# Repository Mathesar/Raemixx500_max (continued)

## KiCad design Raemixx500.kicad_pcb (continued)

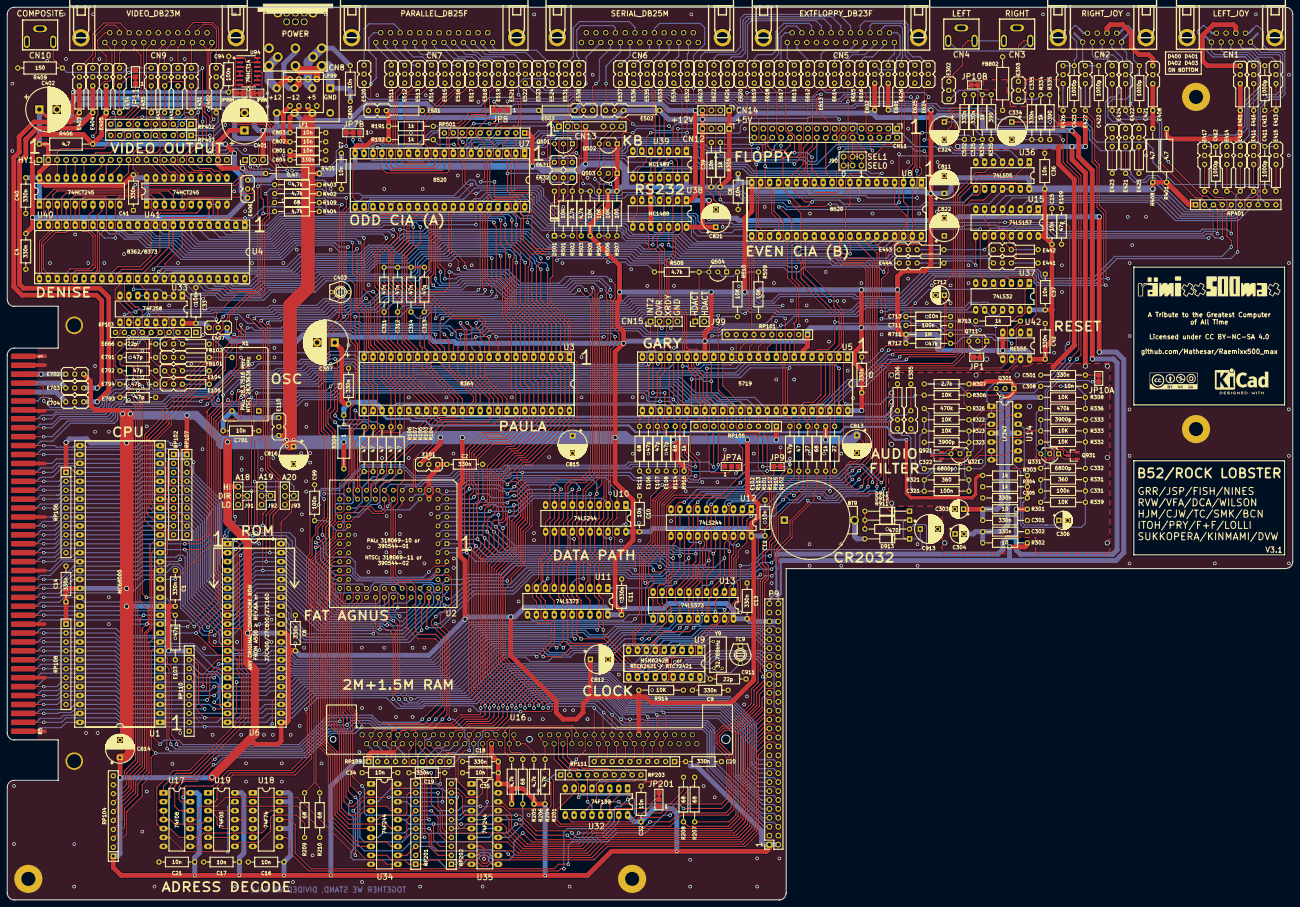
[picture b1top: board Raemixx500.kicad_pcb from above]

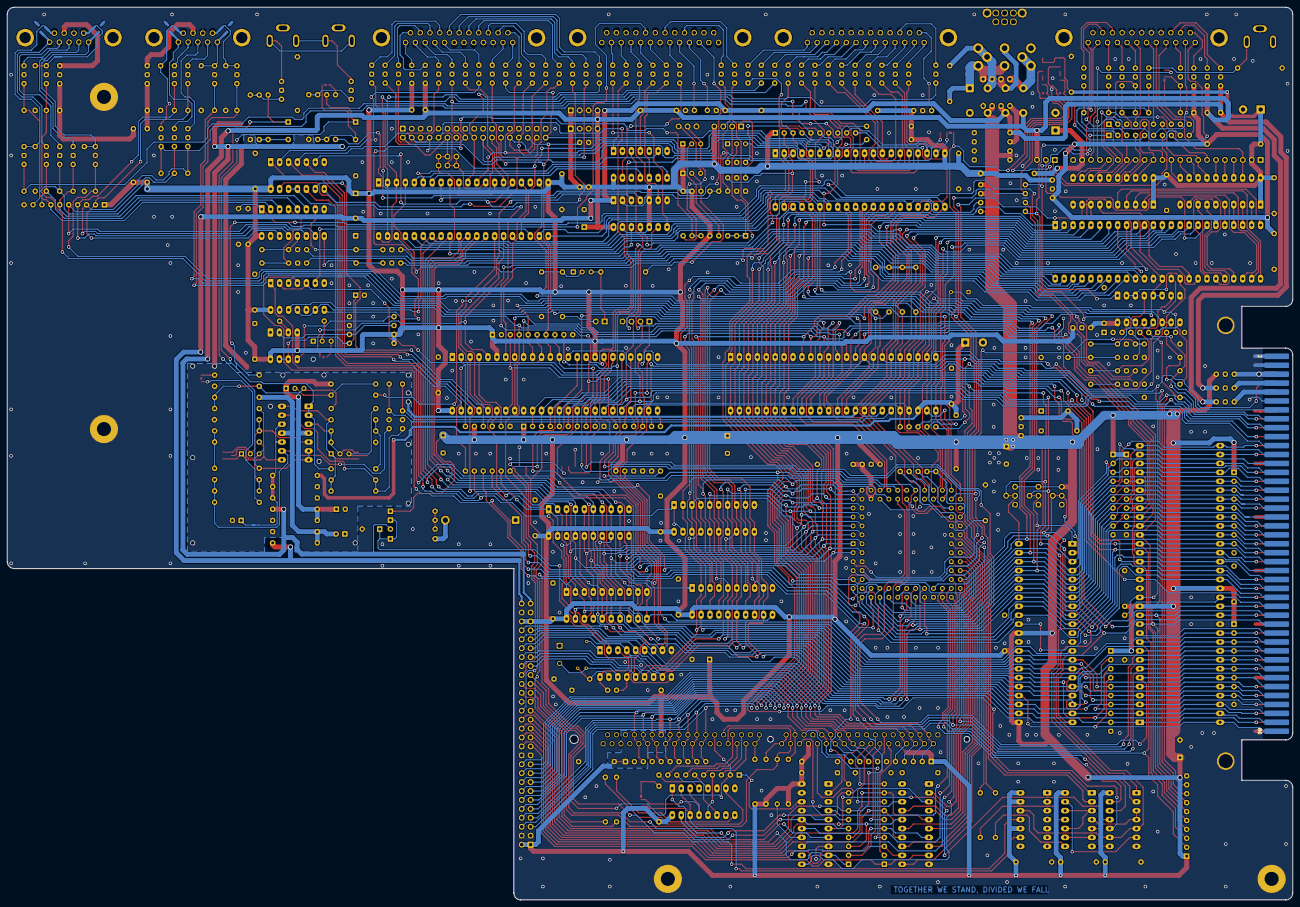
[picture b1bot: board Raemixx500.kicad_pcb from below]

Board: 2 copper layers, 365.8 x 254.0 mm, 372 parts (4 on the bottom side), 488 nets.

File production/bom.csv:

Designator,Footprint,Quantity,Value,LCSC Part #
BT9,Battery_Holder_Coin_2032_BS-7,1,CR2032,
"C1, C11, C13, C14, C16, C17, C18, C19, C2, C20, C3, C4, C40, C41, C42, C5, C6, C804, C9",C_Axial_L6.3mm_D2.5mm_P10.16mm,19,330n,
"C10, C12, C15, C32, C33, C34, C35, C36, C37, C7, C701, C8, C800, C801, C802, C803",C_Axial_L6.3mm_D2.5mm_P10.16mm,16,10n,
"C301, C302, C305, C325, C335, C501, C502",C_Axial_L9.0mm_D3.2mm_P12.70mm,7,330n,
"C303, C304",CP_Radial_D5.0mm_P2.50mm,2,22u,
"C306, C712",CP_Radial_D5.0mm_P2.50mm,2,10u,
"C307, C401, C402",CP_Radial_D12.5mm_P5.00mm,3,1000u,
"C308, C39, C713",C_Axial_L9.0mm_D3.2mm_P12.70mm,3,10n,
"C311, C312, C313, C314",C_Axial_L9.0mm_D3.2mm_P12.70mm,4,47n,
"C321, C331, C711",C_Axial_L9.0mm_D3.2mm_P12.70mm,3,100n,
"C322, C332",C_Axial_L9.0mm_D3.2mm_P12.70mm,2,6800p,
"C323, C333",C_Axial_L9.0mm_D3.2mm_P12.70mm,2,3900p,
"C324, C334",CP_Radial_D8.0mm_P5.00mm,2,22u,
C403,VariCap,1,47p,
"C411, C412, C413, C421, C422, C423",C_Axial_L9.0mm_D3.2mm_P12.70mm,6,1000p,
"C811, C812, C813, C814, C815, C816",CP_Radial_D8.0mm_P5.00mm,6,100u,
"C821, C822",CP_Radial_D8.0mm_P5.00mm,2,47u,
"C911, E666",C_Axial_L6.3mm_D2.5mm_P10.16mm,2,22p,
C913,CP_Radial_D8.0mm_P5.00mm,1,4.7u,
"C94, C99",C_Axial_L6.3mm_D2.5mm_P10.16mm,2,100n,
CN1,DB_9M,1,LEFT_JOY,
CN10,SWITCHCRAFT_PJRAN1X1U01X,1,COMPOSITE,
CN11,IDC-Header_2x17_P2.54mm_Vertical,1,INTERNAL_FLOPPY,
CN12,PinHeader_1x04_P2.54mm_Vertical,1,FLOPPY_POWER,
CN13,Keyboard_Connector,1,KEYBOARD,
CN14,PinHeader_1x04_P2.54mm_Vertical,1,IDE_POWER,
CN15,PinHeader_1x04_P2.54mm_Vertical,1,IDE_I/F,
CN2,DB_9M,1,RIGHT_JOY,
CN3,SWITCHCRAFT_PJRAN1X1U01X,1,RIGHT,
CN4,SWITCHCRAFT_PJRAN1X1U01X,1,LEFT,
CN5,DB_23F,1,EXTFLOPPY_DB23F,
CN6,DB_25M,1,SERIAL_DB25M,
CN7,DB_25F,1,PARALLEL_DB25F,
CN8,DS215+DIN8_COMBO,1,POWER,
CN9,DB_23M,1,VIDEO_DB23M,
"D501, D911, D912, D913",D_DO-35_SOD27_P12.70mm_Horizontal,4,1N4148,
"E101, E110, E406, E407, E702, E703, E704",EMI_Filter_Short,7,10n,
"E102, E103, E106, E107, E108",C_Axial_L9.0mm_D3.2mm_P12.70mm,5,47p,
"E104, E105, FB101",EMI_Filter_Long,3,68,
"E109, E791, E792, E793, E794",C_Axial_L6.3mm_D2.5mm_P10.16mm,5,47p,
"E302, E303",EMI_Filter_Short,2,6800p,
"E305, E306",EMI_Filter_Long,2,270p,
"E401, E403, E404, E405, E408, E601, E602",EMI_Filter_Long,7,10n,
"E402, E434",EMI_Filter_Long,2,150p,
"E411, E412, E413, E414, E421, E422, E423, E424",EMI_Filter_Long,8,6800p,
"E415, E416, E417, E425, E426, E427, E441, E442, E443, E444",EMI_Filter_Long,10,470p,
"E431, E432, E433, E435",EMI_Filter_Long,4,FERR,
"E501, E502, E503",EMI_Filter_Longer,3,47 1/2W,
"E511, E512, E513, E514, E515, E516, E517, E518, E519, E521, E522, E523, E524, E611, E612, E613, E614, E615, E616, E617, E618, E619, E620, E621, E622, E623, E624, E625, E626, E631, E632",EMI_Filter_Short,31,100p,
"E520, E531, E533, E535, E536, E537, E538",EMI_Filter_Short,7,470p,
"E532, E534",EMI_Filter_Short,2,150p,
FB102,EMI_Filter_Long,1,150,
FB802,Ferrite_Axial_L9.0mm_D3.2mm_P12.70mm,1,Ferrite_Bead_Small,
HY1,PinHeader_1x22_P2.54mm_Vertical,1,VIDIOT,
HY2,PinHeader_1x03_P2.54mm_Vertical,1,COLOR_ANNEX,
J90,DriveSwitchHeader,1,DRIVE_SWITCHER,
"J91, J92, J93",Dispatcher_3to1,3,Dispatcher_3to1,
J99,PinHeader_1x01_P2.54mm_Vertical,1,CONN_HDACT,
"JP1, JP10A1, JP10B1, JP99H1, JP99V1",Jumper2-Bridged,5,Jumper_2_Bridged,
JP11,Jumper3-Bridged12,1,Jumper_3_Bridged12,
"JP201, JP7B1, JP8",Jumper3-Bridged23,3,Jumper_3_Bridged23,
JP7A1,Jumper3-Open,1,Jumper_3_Open,
JP9,Jumper2-Open,1,Jumper_2_Open,
LF1,LineFilter,1,L,
LF99,CM4545Z131B-10,1,CM4545Z131B-10,
"MT1, MT2, MT4, MT5, MT6, MT7",MountingHole_4mm_Pad,6,MountingHole_Pad,
P1,A500_SIDE_SLOT,1,EXPANSION BUS,
P9,Trapdoor,1,TRAPDOOR,
"Q301, Q502, Q503, Q99",TO-92L_Inline_Wide,4,2N3906,
"Q321, Q331",TO-92L_Inline_Wide,2,MPF102,
"Q501, Q711",TO-92L_Inline_Wide,2,2N3904,
"Q921, Q931",SOT-23_LongerPads,2,MMBFJ113,
"R101, R102",R_Axial_DIN0309_L9.0mm_D3.2mm_P12.70mm_Horizontal,2,27,
"R103, R104, R105, R106, R107, R113",R_Axial_DIN0309_L9.0mm_D3.2mm_P12.70mm_Horizontal,6,47,
"R109, R111, R112, R114, R206, R207, R208, R209, R210",R_Axial_DIN0309_L9.0mm_D3.2mm_P12.70mm_Horizontal,9,68,
"R191, R192, R303, R304, R305, R324, R334, R713, R915, R916",R_Axial_DIN0309_L9.0mm_D3.2mm_P12.70mm_Horizontal,10,1k,
"R201, R204, R205, R402, R403, R404, R503, R504",R_Axial_DIN0309_L9.0mm_D3.2mm_P12.70mm_Horizontal,8,4.7k,
"R301, R302",R_Axial_DIN0309_L9.0mm_D3.2mm_P12.70mm_Horizontal,2,10,
"R306, R308, R322, R323, R332, R333, R339, R501, R505, R506, R914, R98",R_Axial_DIN0309_L9.0mm_D3.2mm_P12.70mm_Horizontal,12,10k,
"R307, R502",R_Axial_DIN0309_L9.0mm_D3.2mm_P12.70mm_Horizontal,2,2.7k,
R309,R_Axial_DIN0309_L9.0mm_D3.2mm_P15.24mm_Horizontal,1,10,
"R321, R331",R_Axial_DIN0309_L9.0mm_D3.2mm_P12.70mm_Horizontal,2,360,
"R325, R335",R_Axial_DIN0309_L9.0mm_D3.2mm_P12.70mm_Horizontal,2,390,
"R326, R336",R_Axial_DIN0309_L9.0mm_D3.2mm_P12.70mm_Horizontal,2,470k,
"R401, R406, R408",R_Axial_DIN0309_L9.0mm_D3.2mm_P15.24mm_Horizontal,3,4.7,
R405,R_Axial_DIN0309_L9.0mm_D3.2mm_P15.24mm_Horizontal,1,0.47,
R409,R_Axial_DIN0309_L9.0mm_D3.2mm_P12.70mm_Horizontal,1,150,
R507,R_Axial_DIN0309_L9.0mm_D3.2mm_P12.70mm_Horizontal,1,100,
R711,R_Axial_DIN0309_L9.0mm_D3.2mm_P12.70mm_Horizontal,1,1M,
"R712, R99",R_Axial_DIN0309_L9.0mm_D3.2mm_P12.70mm_Horizontal,2,47k,
R911,R_Axial_DIN0309_L9.0mm_D3.2mm_P12.70mm_Horizontal,1,470,
"RP101, RP102, RP105, RP106, RP107, RP108, RP109, RP110, RP111, RP401",R_Array_SIP10,10,4.7k,
RP103,R_Array_SIP10,1,39,
RP104,R_Array_SIP10,1,470,
"RP201, RP202, RP203",R_Array_SIP10,3,68,
"RP402, RP403",R_Array_SIP10,2,47,
RP501,R_Array_SIP10,1,10k,
TC9,VariCap,1,6.8-45p,
U1,DIP-64_W22.86mm_Socket_LongPads,1,68000D,
"U10, U12, U34, U35",DIP-20_W7.62mm_Socket_LongPads,4,74LS244,
"U11, U13",DIP-20_W7.62mm_Socket_LongPads,2,74LS373,
U14,DIP-14_W7.62mm_Socket_LongPads,1,LF347,
U15,DIP-16_W7.62mm_Socket_LongPads,1,74LS157,
U16,SIMM_TE_Connectivity_5822134-3,1,SIMM,
U17,DIP-14_W7.62mm_Socket_LongPads,1,74LS08,
U18,DIP-14_W7.62mm_Socket_LongPads,1,74LS74,
U19,DIP-14_W7.62mm_Socket_LongPads,1,74F00,
U2,PLCC-84_THT-Socket,1,FAT_AGNUS_8375,
U3,DIP-48_W15.24mm_Socket_LongPads,1,PAULA,
U32,DIP-16_W7.62mm_Socket_LongPads,1,74LS139,
U33,DIP-16_W7.62mm_Socket_LongPads,1,74LS258,
U36,DIP-14_W7.62mm_Socket_LongPads,1,74LS05,
U37,DIP-14_W7.62mm_Socket_LongPads,1,74LS32,
U38,DIP-14_W7.62mm_Socket_LongPads,1,MC1488,
U39,DIP-14_W7.62mm_Socket_LongPads,1,MC1489,
U4,DIP-48_W15.24mm_Socket_LongPads,1,DENISE,
"U40, U41",DIP-20_W7.62mm_Socket_LongPads,2,74LS245,
U42,DIP-8_W7.62mm_Socket_LongPads,1,NE555,
U5,DIP-48_W15.24mm_Socket_LongPads,1,GARY_5719,
U6,DIP-42_W15.24mm_Socket_LongPads,1,ROM,
"U7, U8",DIP-40_W15.24mm_Socket_LongPads,2,VIA_8520,
U9,DIP-18_W7.62mm_Socket_LongPads,1,MSM6242B,
"U90, U91, U92, U93",TSOP-6_Handsolder,4,DT1042,
U94,SOIC-14_3.9x8.7mm_P1.27mm,1,74HCT14,
V0,cc_by_nc_sa,1,OSHW_LOGO,
V1,KiCad-Logo2_6mm_SilkScreen,1,KICAD_LOGO,
V2,Logo,1,PROJ_LOGO,
X1,Oscillator_DIP-14,1,XTAL,
Y9,Crystal_RTC,1,32768,

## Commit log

2026-02-22 schematic imported into KiCad 9 and fixed annotation errors and more due to import.
2026-02-22 PCB file converted to KiCad 9.
2026-02-22 fixed DRC warning on bridged jumpers
2026-02-23 cleaned up side connector footprint to get rid of DRC errors
2026-02-23 fixed courtyards
2026-02-24 pin 1 and 3 were swapped
2026-02-25 fixed annular ring DRC on SUB-D and at the same time made all SUB-D footprints the same
2026-02-25 updated changed footprints
2026-02-25 updated readme with warning this project is work in progress
2026-02-28 fixed some schematic parity DRC warnings.
2026-02-28 belongs to previous commit, fixed schematic parity DRC errors
2026-02-28 Added footprint for 72pin SIMM
2026-03-01 added symbol for 72pin SIMM
2026-03-05 added separate power unit for SIMM
2026-03-10 added 3D model for SIMM module
2026-03-13 DRAM chips replaced with SIMM module
    Added logic to decode 2MB chip + 1.5MB slow
    Rewired trapdoor slot
2026-03-14 optimized timing
    removed CCK from RAM buffers to ease routing
2026-03-15 removed JP2
    some more small fixes
    schematic is now more or less done I think
2026-03-18 routing SIMM
    work in progress
2026-03-21 changed wiring of pullups, simplified SIMM parity pullups
    Routed more nets. Slowly getting there. WIP
2026-03-22 More work done, routing of SIMM module datapath almost done
2026-03-22 oops!
2026-03-25 Completed routing, no DRC errors (but still a lot of warnings)
    TODO: thoroughly review all small schematic changes
2026-03-26 fixed bug in CAS multiplexer
    added logo
2026-03-26 added teardrops
2026-03-26 added production directory to .gitignore
2026-03-28 removed some unnecessary copper zones
    improved grounding around SIMM a bit
2026-04-01 small optimizations
2026-04-01 Improved HDD LED circuitry so that positive drive LEDs are also supported
    More routing improvements
2026-04-06 - some IC are not socketed anymore to fit under shield
    - updated logo
    - silkscreen cleanup
    - added pin1 indicator to solder jumpers
2026-04-08 removed ESD diodes
2026-04-09 Fixed some very nasty shorts that happened many commits ago when the design was imported into KiCad9.
2026-04-09 removed some via's that I put to connect ground traces together.
    Now that the shorted nets have been fixed, these traces are no longer ground....
2026-04-09 Added back ESD diodes very close to sensitive pins only for more effective protection
    Made teardrops as small as possible
2026-04-10 added silkscreen on top for ESD diodes on bottom
    added special symbol for keyboard header to get rid of schematic parity error
2026-04-11 Started cleaning up BOM
2026-04-11 Updated readme with more warning that this is work in progress
2026-04-12 Working on BOM
2026-04-14 more work on BOM done
2026-04-15 More BOM work
    I am marking optional components as DNP to get some overview
2026-04-19 BOM updates
2026-04-19 BOM work done
2026-04-19 even more BOM work
2026-04-19 added mouser part numbers
2026-04-25 replaced commodore hybrid with OpenAmigaVideoHybrid
    decided to place address pullups for better EPROM capability
2026-04-26 added pin 1 indications like on originnal board
    changed floppy connector to non-shrouded version
2026-04-26 more silkscreen work
    removed sockets for standard IC's
2026-04-26 even more silkscreen refinements
2026-04-26 more refinements
2026-04-26 made one trace better looking :-)
2026-05-13 gitignore
2026-05-19 fixed R309 wrong value
    Replaced too big 2W resistors with better fitting 1W resistors
2026-05-21 increased hole size of variable capacitor footprint
2026-05-30 added CAD model for MFP920 floppy eject button
2026-05-30 Added CAD model for Sony MFP920 to Chinon button.
    The Chinon button needs some cutting away
2026-06-20 updated PCB with schematics and footprint changes
2026-06-20 moved floppy connector 0.3mm away from audio output connectors
    bumped version on schematics and PCB to V3.1
2026-06-21 added more clearance for drive frame and PCB
2026-06-21 slightly moved location of eject button for a better fit
2026-06-21 updated chinon to sony eject button with latest changes
2026-06-21 README updated
2026-06-22 more README updates
2026-06-22 typos corrected
2026-06-23 added step files for MFP920 eject buttons
    updated README
2026-06-23 Added pictures of MFP920 Eject buttons.
    Updated README again.
2026-06-23 new smaller image
